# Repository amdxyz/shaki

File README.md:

# AMDX Shaki

Push - Shake - Love: that's as simple as how the "Shaki" works. If you push a button and shake the stick, a message, a name or a symbol appears in the air. But what the Shaki actually demonstrates is a highly complex phenomenon - the Persistence of vision.

## POV

POV stands for Persistence of vision (https://en.wikipedia.org/wiki/Persistence_of_vision)
The image of an object stays on the retina even after stopping looking at it as the eye and brain actually retain a visual impression for about 1/20 th of a second. It is the principle of movies and animations - and of the small exhibit we at Archimedes Exhibitions created to make this scientific phenomenon playfully comprehensive. You can put the Shaki in your trouser pocket and experience and learn about the Persistence of vision wherever you like, alone or in groups.

## History

The Shaki was developed as part of an internal competition we regularly launch at Archimedes Exhibitions to cultivate creativity and innovative ideas outside the daily working routine. The goal of the competition was to produce a cheap and insightful giveaway for the upcoming ECSITE annual conference (https://www.ecsite.eu/).

The background idea behind our Shaki was kind of a „Gadgetification": taking one of our original size exhibits and shrinking it until it fits into a trouser pocket.

The Shaki is the gadgetified version of our "Spinning Display", a rotating POV display developed for the Science and Technology Centre Ostrava (CZ), as part of the "World of Nature" exhibition (http://stcostrava.cz/setrvacnost-oka).

Archimedes Exhibitions gave away 200 Shakis units among the participants of the 2018 ECSITE conference and, after its big success, decided to release the Shaki's firmware, tools and PCB as open source.

## Components and operation

The Shaki hardware has five main components:

* battery: its power source
* button: connects the battery to the rest of the components
* microcontroller: the brain
* accelerometer: the sensor that detects a shake
* LEDs bar: 8 small light emitting diodes that paint the stored pictures in the air

### Theory of operation

Once the button is pressed and as long as it's being kept pressed, the microcontroller talks to the accelerometer and attempts to detect the motion of the stick in real time. The accelerometer reports its readouts 1.600 times per second.

The idea is to detect the two extremes of a shake motion (a rapid side to side oscillation) and to paint a frame while moving from left to right.

As soon as the microcontroller decides that the stick is moving from left to right, it starts to stream the current frame to the LEDs bar. The frame is composed of several columns and each column is extracted and "transferred" to the LEDs bar using a timer. This transfer means that some LEDs will be lit, some not, according to the "white" or "black" pixels set in the frame.

Each 2.4ms a new column is moved from the microcontroller's memory to the LEDs bar until all the columns have been transferred. From this point on the LEDs shut down and the microcontroller waits until the rightmost point is reached.

Once the rightmost point is reached, the microcontroller decides whether to advance to the next frame or to paint the last one again (depending on the amount of shakes-per-frame defined). The LEDs are kept off until the cycle repeats.

### More details on the components

* Microcontroller: ATMEL ATTiny88 (8kB FLASH, 512B SRAM) clocked at 8Mhz via its internal RC oscillator
* Accelerometer: ST LIS3DH MEMS accelerometer (16bit, I2C/SPI, 5300Hz max update rate)

The accelerometer is connected to the microcontroller via its I2C interface.

## What to find in the repository

This repository is composed of the following:

* eagle: EagleCAD schematics, PCB layout and BOM
* firmware: the software that runs inside the Shakis
* tools: converter and authoring tools to customise the displayed frames

Each folder contains a detailed readme file.

## FAQ

AKA frequently asked questions:

### Can I get an assembled, ready-to-use Shaki?

Yes, write to us: shaki {a} amdx.de

### Can I produce, customise, sell the Shaki?

As long as it fits the terms of the [LICENSE](https://github.com/amdxyz/shaki/blob/master/LICENSE.md), you're more than welcome.

### How can I customise my Shaki?

This repository provides everything you need to do any customisation you may have in mind, but the process requires some technical skills and tools.

In short:

* Produce the frames using a graphic authoring tool or the included of_bitpuncher tool
* Convert the authored graphic (not required when using of_bitpuncher)
* Compile the firmware
* Upload the firmware to the Shaki using a programmer and a programming jig

### Why no USB?

One of the Shaki's primary requirements was to minimize its production costs. It wasn't initially supposed to be released to the public, so we didn't consider a consumer-grade programming interface.

### How can I contribute?

Feel free to file an issue or post a push request!

### Any media?

You can watch a short presentation here: https://www.youtube.com/watch?v=L5a6pu70XJo

And a brief introduction here: http://www.amdx.de/shaki

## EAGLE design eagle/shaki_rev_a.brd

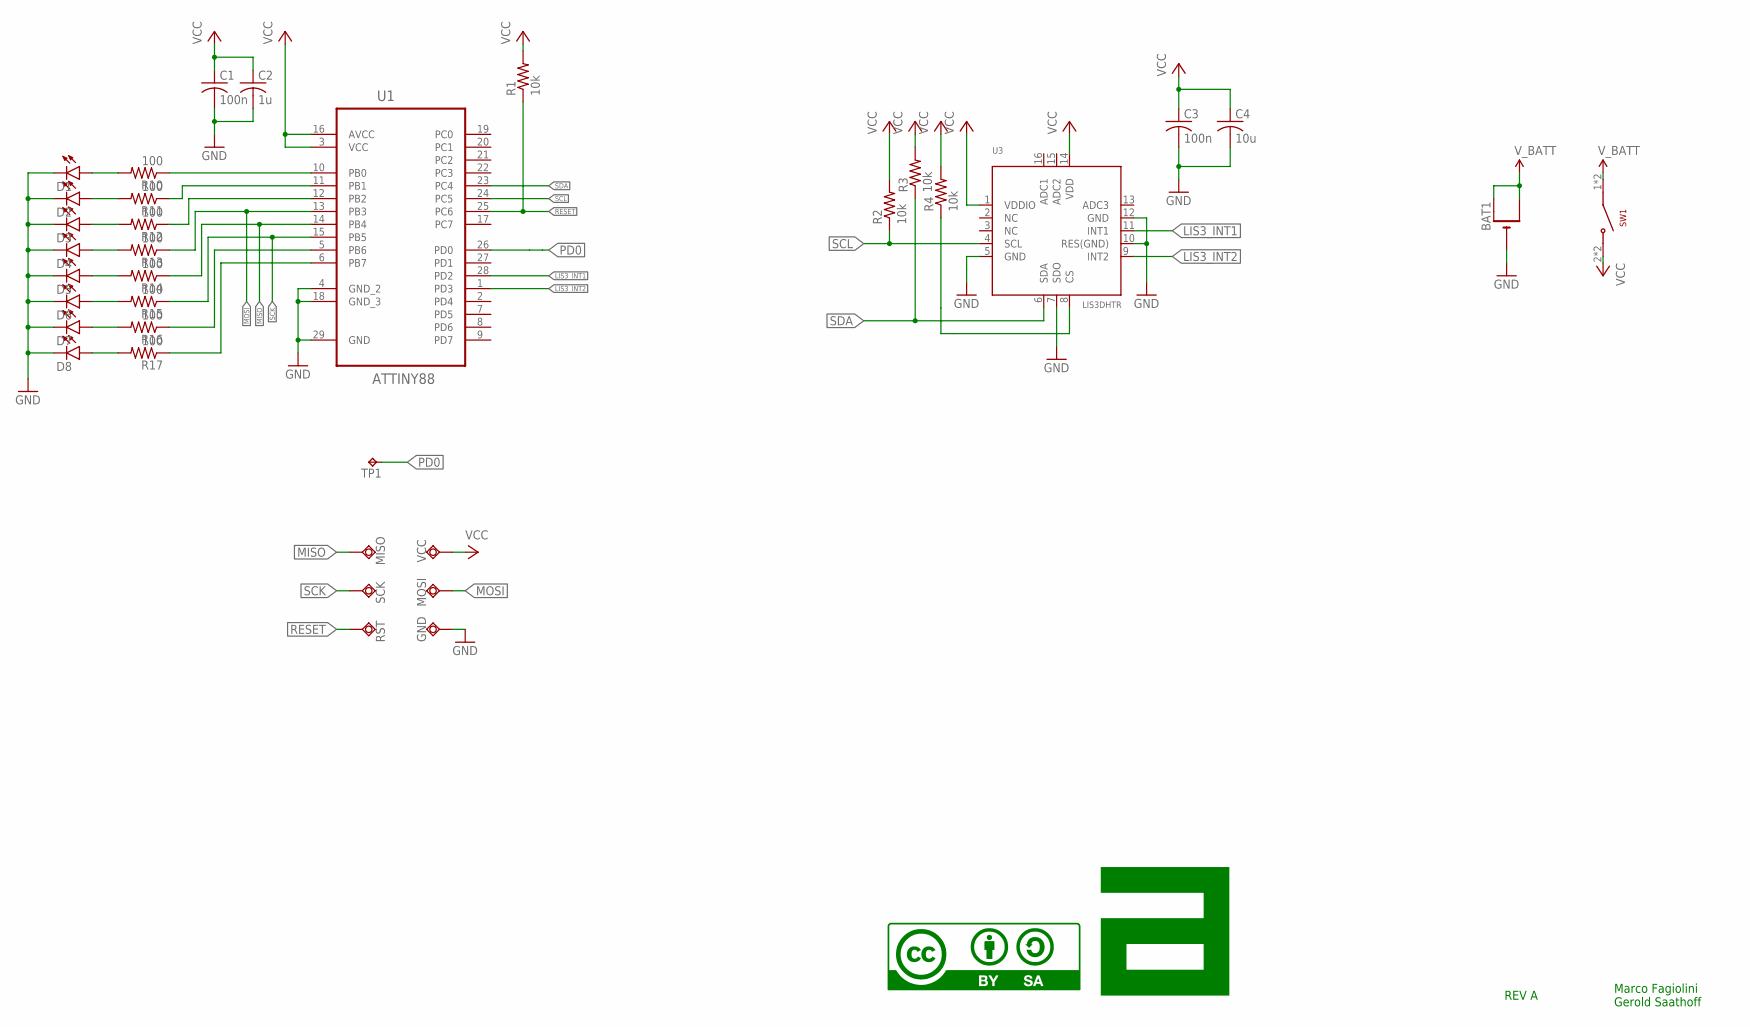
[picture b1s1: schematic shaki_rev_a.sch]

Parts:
BAT1: CR1220SMT; CR1220-SMD
C1, C3: 100n; C0603K
C2: 1u; C0603K
C4: 10u; C0603K
D1, D2, D3, D4, D5, D6, D7, D8: LED0603; LED-0603
GND: TPSQTP13R; TP13R
MISO: TPSQTP13R; TP13R
MOSI: TPSQTP13R; TP13R
R1, R2, R3, R4: 10k; 0603
R10, R11, R12, R13, R14, R15, R16, R17: 100; 0603
RST: TPSQTP13R; TP13R
SCK: TPSQTP13R; TP13R
SW1: SKRRABE010
TP1: TESTPAD
U1: ATTINY88; QFN45P400X400X100-29N
U3: LIS3DHTR; LGA16_3X3MM
VCC: TPSQTP13R; TP13R

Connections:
GND: BAT1.-, C1.2, C2.2, C3.2, C4.2, D1.C, D2.C, D3.C, D4.C, D5.C, D6.C, D7.C, D8.C, GND.TP, U1.4 (GND_2), U1.18 (GND_3), U1.29 (GND), U3.5 (GND), U3.7 (SDO), U3.10 (RES(GND)), U3.12 (GND)
LED1: R10.1, U1.10 (PB0)
LED2: R11.1, U1.11 (PB1)
LED3: R12.1, U1.12 (PB2)
LED7: R16.1, U1.5 (PB6)
LED8: R17.1, U1.6 (PB7)
LIS3_INT1: U1.28 (PD2), U3.11 (INT1)
LIS3_INT2: U1.1 (PD3), U3.9 (INT2)
MISO: MISO.TP, R14.1, U1.14 (PB4)
MOSI: MOSI.TP, R13.1, U1.13 (PB3)
unnamed: R4.1, U3.8 (CS)
unnamed: D1.A, R10.2
unnamed: D2.A, R11.2
unnamed: D3.A, R12.2
unnamed: D4.A, R13.2
unnamed: D5.A, R14.2
unnamed: D6.A, R15.2
unnamed: D7.A, R16.2
unnamed: D8.A, R17.2
PD0: TP1.P$1, U1.26 (PD0)
RESET: R1.1, RST.TP, U1.25 (PC6)
SCK: R15.1, SCK.TP, U1.15 (PB5)
SCL: R2.1, U1.24 (PC5), U3.4 (SCL)
SDA: R3.1, U1.23 (PC4), U3.6 (SDA)
VCC: C1.1, C2.1, C3.1, C4.1, R1.2, R2.2, R3.2, R4.2, SW1.2, SW1.4 (2), U1.3 (VCC), U1.16 (AVCC), U3.1 (VDDIO), U3.14 (VDD), VCC.TP
V_BATT: BAT1.+$1 (+), BAT1.+$2 (+1), SW1.1, SW1.3 (1)

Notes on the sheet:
REV A
Marco Fagiolini Gerold Saathoff

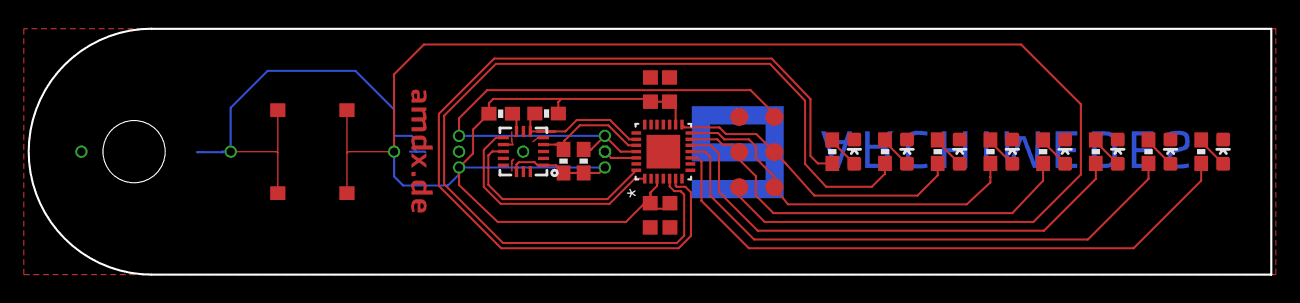
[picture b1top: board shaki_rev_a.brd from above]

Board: 2 copper layers, 89.8 x 17.8 mm, 35 parts (1 on the bottom side), 26 nets.

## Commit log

2018-07-21 Initial import for github

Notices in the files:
parts and their libraries:
SparkFun-LED: Licensing: Creative Commons ShareAlike 4.0 International - https://creativecommons.org/licenses/by-sa/4.0
microbuilder: This work is placed in the public domain, and may be freely used for commercial and non-commercial work with the following conditions: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
